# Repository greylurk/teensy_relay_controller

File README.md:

This is an interface from the Teensy 3.0 controller to a SainSmart 4 channel 
relay.

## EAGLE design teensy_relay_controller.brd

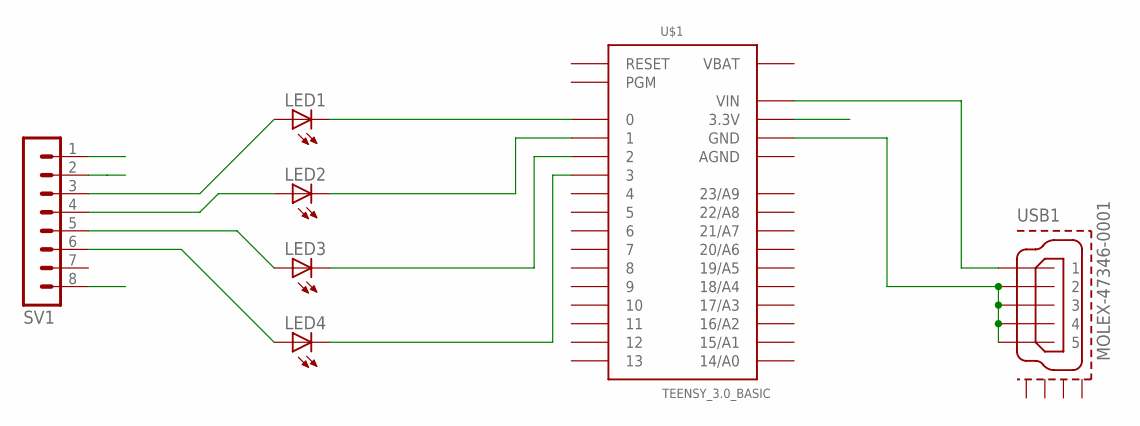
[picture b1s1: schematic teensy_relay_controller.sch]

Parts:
LED1, LED2, LED3, LED4: LED5MM
SV1: MA08-1
U$1: TEENSY_3.0_BASIC
USB1: MOLEX-47346-0001; MOLEX-47364-0001

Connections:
3.3V_VCC: SV1.2, U$1.3.3V, U$1.3.3V1 (3.3V)
5V_VCC: SV1.1, U$1.VIN, USB1.1
AGND: U$1.AGND
GND: SV1.8, U$1.GND, U$1.GND1 (GND), USB1.2, USB1.3, USB1.4, USB1.5
unnamed: LED2.K (C), U$1.1
unnamed: LED3.K (C), U$1.2
unnamed: LED4.K (C), U$1.3
unnamed: LED1.A, SV1.3
unnamed: LED3.A, SV1.5
unnamed: LED4.A, SV1.6
VBAT: U$1.VBAT
_RELAY3: LED2.A, SV1.4
_RELAY4: LED1.K (C), U$1.0

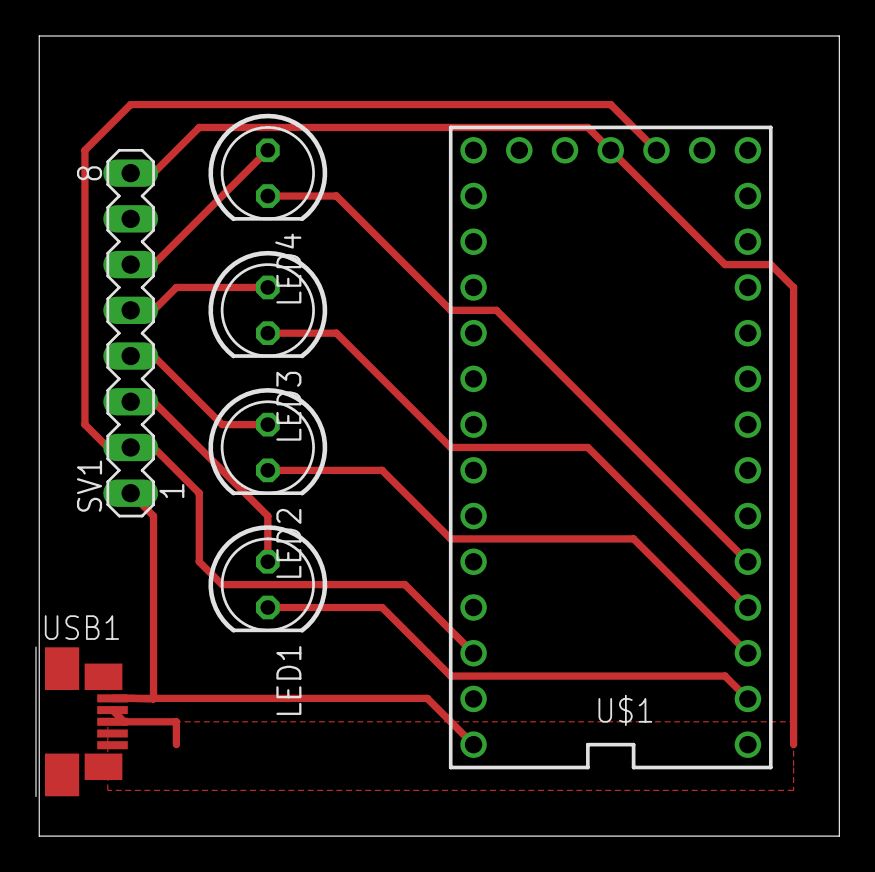
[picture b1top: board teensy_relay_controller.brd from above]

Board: 2 copper layers, 44.6 x 44.4 mm, 7 parts (0 on the bottom side), 11 nets.

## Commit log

2013-11-17 First Draft
2013-11-17 Cleaning up the size of the board abit
2013-11-17 Adding Readme file
